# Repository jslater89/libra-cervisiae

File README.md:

# Libra Cervisiae

Libra Cervisiae is an ESP8266-powered microcontroller for reading output from a high-precision scale, used to weigh beer to measure the progress of its fermentation.

Development updates can be found at the project's [github pages site](https://jslater89.github.io/libra-cervisiae).

## History
Libra Cervisiae used to be Pendulum, which was itself once a tilting hydrometer (abandoned for patent reasons) and once a weigh-a-sinker hydrometer (abandoned for DIY difficulty reasons).

Libra Cervisiae has its root in experiments done in the 1990s on measuring fermentation progress by CO2 production, and more recent experiments done by forumgoers at [Homebrewtalk](https://www.homebrewtalk.com/forum/threads/estimating-alcohol-by-total-weight-during-fermentation.265716/#post-6913352) and [Hobbybrouwen.nl](https://www.hobbybrouwen.nl/forum/index.php/topic,35958.0.html).

## Design
Libra Cervisiae is a microcontroller and PCB project. The project is designed with easy DIY in mind, and as such, the PCB uses large, easy-to-solder surface mount components, as well as breakout boards for the major, non-ESP8266 integrated circuits.

The project as specified here includes building a scale of your own, but the microcontroller's design ought to allow for hacking existing scales of the correct capacity, too.

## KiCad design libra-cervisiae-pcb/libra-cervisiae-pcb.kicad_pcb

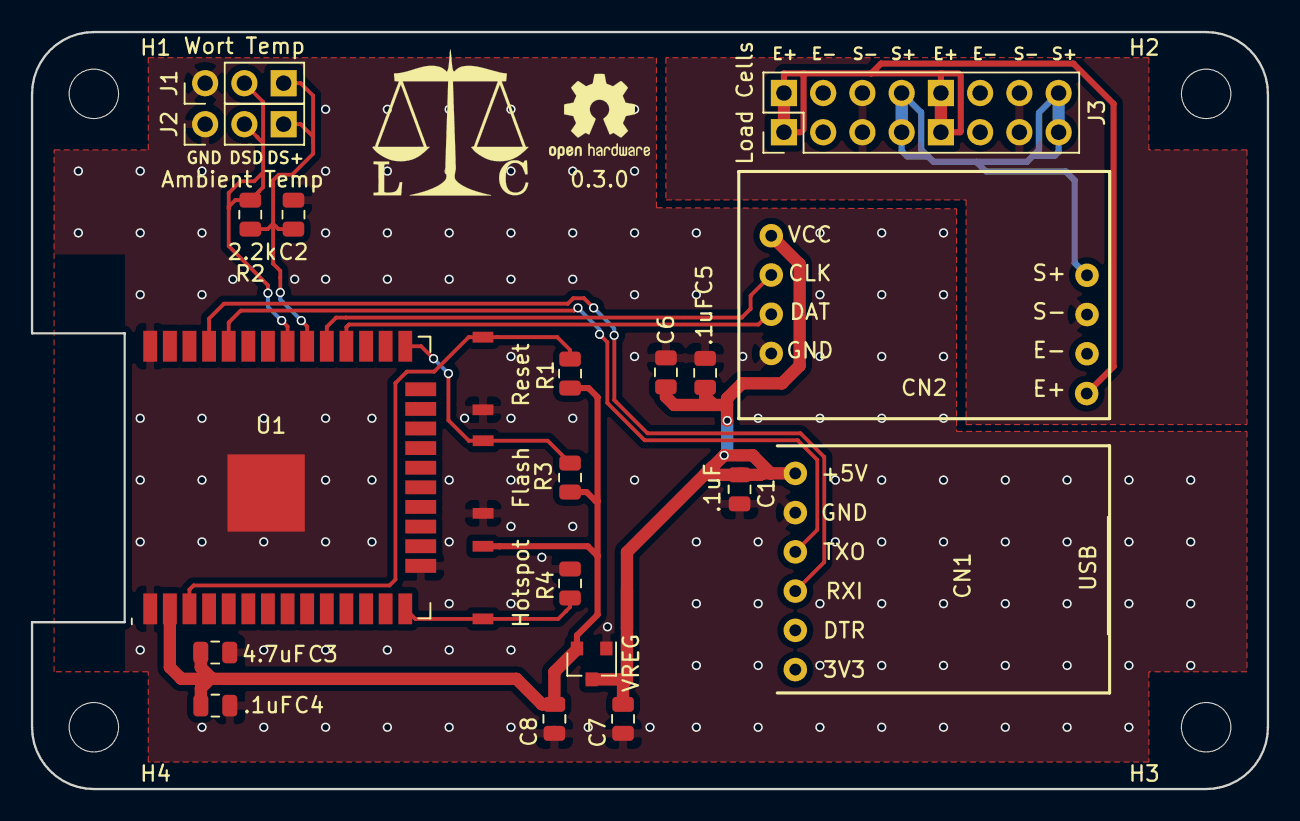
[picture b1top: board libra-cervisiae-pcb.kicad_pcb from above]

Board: 2 copper layers, 80.0 x 49.0 mm, 26 parts (0 on the bottom side), 16 nets.

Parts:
C1, C4, C5: .1uF; C_0805_2012Metric
C2, C6, C7, C8: 1uF; C_0805_2012Metric
C3: 4.7uF; C_0805_2012Metric
CN1: CP2102-BREAKOUT
CN2: HX711_BREAKOUT; HX711-MINI
H1, H2, H3, H4: MountingHole_3.2mm_M3
J1: Wort Temp; PinHeader_1x03_P2.54mm_Vertical
J2: Ambient Temp; PinHeader_1x03_P2.54mm_Vertical
J3: Load Cells; PinHeader_2x08_P2.54mm_Vertical
R1, R3, R4: 10k; R_0805_2012Metric
R2: 2.2k; R_0805_2012Metric
SW1: Reset; 4x3_Switch
SW2: Flash; 4x3_Switch
SW3: Hotspot; 4x3_Switch
U1: ESP32-WROOM-32
U2: VREG; SOT-23

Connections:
/3.3+: C3.2, C4.2, C8.2, R1.2, R3.2, SW3.1, U1.2, U2.2
/CLK: CN2.9, U1.29
/DAT: CN2.8, U1.28
/DS+: C2.2, J1.3, J2.3, R2.2, U1.30
/DSD: J1.2, J2.2, R2.1, U1.31
/E+: CN2.1, J3.1, J3.5, J3.9, J3.13
/E-: CN2.2, J3.2, J3.6, J3.10, J3.14
/GND: C1.1, C2.1, C3.1, C4.1, C5.1, C6.1, C7.1, C8.1, CN1.5, CN2.10, J1.1, J2.1, R4.1, SW1.2, SW2.1, U1.1, U1.15, U1.38, U1.39, U2.1
/HostRX: CN1.3, U1.35
/HostTX: CN1.4, U1.34
/S+: CN2.4, J3.4, J3.8, J3.12, J3.16
/S-: CN2.3, J3.3, J3.7, J3.11, J3.15
/USB+: C1.2, C5.2, C6.2, C7.2, CN1.6, CN2.7, U2.3
unnamed: R1.1, SW1.1, U1.3
unnamed: R3.1, SW2.2, U1.25
unnamed: R4.2, SW3.2, U1.14

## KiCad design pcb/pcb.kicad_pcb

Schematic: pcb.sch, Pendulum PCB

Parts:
C1, C5: 47uF; C_0805_2012Metric
C2, C3, C4, C8: 1uF; C_0805_2012Metric
C6, C7: 100nF; C_0805_2012Metric
CN1: CP2102-BREAKOUT
CN2: TP4056
CN3: HX711_BREAKOUT; HX711-MINI
D1: SS36; D_SMA
J1: BAT+; SolderWirePad_single_SMD_5x3mm
J2: BAT-; SolderWirePad_single_SMD_5x3mm
J3: Battery; Molex_PicoBlade_53048-0410_1x02_P1.25mm_Horizontal
J4: DS18B20; Molex_PicoBlade_53048-0610_1x03_P1.25mm_Horizontal
J5: TMP+; SolderWirePad_single_SMD_5x3mm
J6: TMPO; SolderWirePad_single_SMD_5x3mm
J7: TMP-; SolderWirePad_single_SMD_5x3mm
J8: WHT; SolderWirePad_single_SMD_5x3mm
J9: BLK; SolderWirePad_single_SMD_5x3mm
J10: GRN; SolderWirePad_single_SMD_5x3mm
J11: RED; SolderWirePad_single_SMD_5x3mm
J12: Load Cell; Molex_PicoBlade_53048-0810_1x04_P1.25mm_Horizontal
Q1: AO3401; SOT-23
R1, R4, R5, R6, R7, R8, R9: 10k; R_0805_2012Metric
R2: 120k; R_0805_2012Metric
R3: 390k; R_0805_2012Metric
SW1: Reset; 4x3_Switch
SW2: Flash; 4x3_Switch
U1: VREG; SOT-23
U2: ESP-12F; ESP-12E

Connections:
/3.3+: C1.1, C3.2, R1.1, R4.2, R5.1, R7.1, U1.2 (VO), U2.8 (VCC)
/ADC: C7.1, R2.1, R3.1, U2.2 (ADC)
/BAT+: CN2.4, J1.1, J3.1, R3.2
/BLK: CN3.2, J9.1, J12.3
/CHG+: CN2.3, Q1.3 (D)
/CLK: CN3.9, U2.14 (GPIO5)
/DAT: CN3.8, U2.13 (GPIO4)
/DS+: C4.2, J4.3, J5.1, R9.1, U2.5 (GPIO14)
/DSD: J4.2, J6.1, R9.2, U2.6 (GPIO12)
/GND: C1.2, C2.1, C3.1, C4.1, C5.2, C6.1, C7.2, C8.1, CN1.5, CN2.2, CN2.6, CN3.10, J4.1, J7.1, R2.2, R6.1, R8.2, SW1.2, SW2.2, U1.1 (GND), U2.9 (GND)
/GRN: CN3.4, J10.1, J12.1
/HX+: C8.2, CN3.7, U2.7 (GPIO13)
/HostRX: CN1.3, U2.16 (TXD)
/HostTX: CN1.4, U2.15 (RXD)
/RED: CN3.1, J11.1, J12.4
/USB+: C6.2, CN1.6, CN2.1, D1.2, Q1.1 (G), R8.1
/VREG+: C2.2, C5.1, D1.1, Q1.2 (S), U1.3 (VI)
/WHT: CN3.3, J8.1, J12.2
unnamed: CN2.5, J2.1, J3.2
unnamed: R1.2, SW1.1, U2.1 (REST), U2.4 (GPIO16)
unnamed: R4.1, U2.3 (CH_PD)
unnamed: R5.2, U2.11 (GPIO2)
unnamed: R6.2, U2.10 (GPIO15)
unnamed: R7.2, SW2.1, U2.12 (GPIO0)

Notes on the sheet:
Battery Pads
MCP1700
Load Cell
Battery Monitor
DS18B20 Molex/Pads
Battery Disconnector

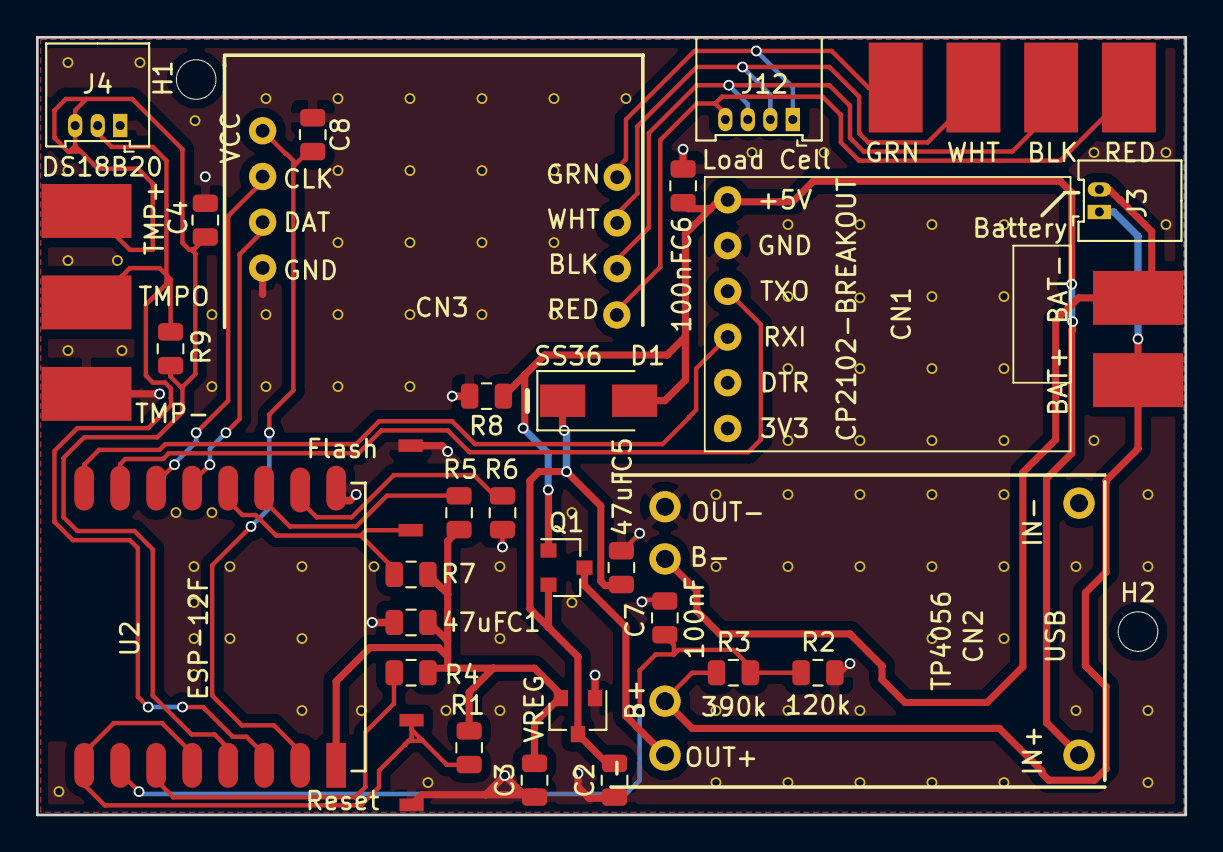
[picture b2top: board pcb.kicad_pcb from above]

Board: 2 copper layers, 63.8 x 43.2 mm, 40 parts (0 on the bottom side), 24 nets.

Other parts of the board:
H1, H2: MountingHole_2.2mm_M2

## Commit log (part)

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2018-05-28 Reorg
2018-05-28 Minor readme update
2018-05-28 README shopping list
2018-05-28 Dummy out some config stuff
2018-05-31 Update config
2018-06-01 Config/hotspot updates, config web page
2018-06-02 README merge
2018-06-03 Add default config file, correct JSONification in main.html
2018-06-03 Add a sensor-handling class for MPU6050 startup/shutdown
    Expects to find the MPU6050 on D5/GPIO14.
2018-06-04 Add voltage reading from A0
    (Wire with a 100kohm resistor.)
2018-06-06 Add output, API config, fix wifi reconnection
2018-06-11 Further shopping list improvements
2018-06-11 Set theme jekyll-theme-slate
2018-06-11 Docs folder
2018-06-14 A custom PCB is probably the best solution in the long run...
    ... so I went ahead and figured one out. Obviously not worth messing
    around with until I've done the whole thing on a breadboard.
2018-06-14 Move KiCad libraries into project
2018-06-14 Move a resistor to line up with another resistor
2018-06-14 Some ongoing minor PCB edits
2018-06-14 PCB blog post
2018-06-15 Clean up traces/vias
2018-06-15 3D model, hide some switch text
2018-06-15 Tweak switch silkscreen labels, add polarity sign to capacitor
    The MCP1700 says a ceramic capacitor is fine, but in case people use
    polar capacitors, it's nice to have an indicator of which way it goes.
    For the switches, remove the redundant SW1/2 label beneath Flash/Reset,
    and just label inside the switch footprint.
2018-06-15 Route I2C traces on opposite side of PCB from ESP-12
    Hopefully to limit interference.
2018-06-15 Further trace cleanup
2018-06-15 Fix problems from Capacitors 101
2018-06-16 Battery etc. blog post
2018-06-16 PCB: use a smaller FTDI breakout board
    The CP2102 USB Micro breakout boards look like they fit between the
    pins of the TP4056 breakout board, which simplifies installation.
2018-06-17 More trace cleanup:
    1. Remove right angles
    2. Thicker USB+/-, charger +/-, 3.3, GND traces
    3. Improve 3.3 and GND routing: more like rails and traces to
    components, less daisy-chaining
2018-06-17 GY521 dimensions update (to match measured size on my workbench)
2018-06-18 Move board in page (ugh)
2018-06-18 Backup file
2018-06-18 Some significant design changes
    Thanks to u/Triabolical_ and u/alez from r/PrintedCircuitBoards for their
    feedback and advice.
    1. Switch to 805 resistors and the non-hand-soldered PCB pad footprints
    They're not appreciably harder to solder, given that they're only 0.01"
    smaller than the 1206 size, and they make routing considerably easier.
    The non-hand-soldered size will be a bit trickier, but not all that
2018-06-18 Add board name, version number, and OSHW logo
2018-06-18 Flip USB-to-serial board so that USB port points outward
2018-06-18 rev 1.0.0-rc.1
2018-06-19 Notes on Tilt patents etc.
2018-06-20 Patent-unencumbered PCB concept
    Tilting is off the table, so let's explore a different idea: weighing
    a sinker immersed in the wort. See the github pages plog for more.
2018-06-20 PCB 1.0.0-rc.2
2018-06-20 README update
2018-06-20 Add a pad for a decoupling capacitor for temperature sensor, just in case
2018-06-20 Measure some pictures of chips to update local parts libraries
    Hopefully it's good enough. Otherwise we'll fix it in rev2.
2018-06-21 Fix some design errors, including a missing connection from 16->RST
2018-06-21 Pendulum Reborn blog post
2018-06-21 Switch to p-channel MOSFET for battery monitor switch
    Because we want as close to zero voltage through the circuit to the
    ADC as possible when the battery monitor is off and the temperature
    sensor is on, we need to switch on the high side, between BAT+ and
    ADC.
    The BSS84 seems like a reasonable choice; its maximum gate threshold
    voltage is well below the difference between ground and a discharged
2018-06-22 DS18B20, 4x3 switch footprint, routing tweaks
    Use a DS18B20 temperature sensor instead of a TMP36. We have enough
    GPIOs—we can drive it from the former SENS2 net (power for the prior
    sensor) and use the former SENS1 net (battery monitor transistor) for
    the data line. This simplifies the ADC circuitry significantly, and
    lets us ditch a bunch of parts.
    Add 4mmx3mm switch footprint, adjust routing as needed.
2018-06-22 PCB.bak
2018-06-24 Another crack at a battery disconnector circuit
    I found an example on the Arduino forums (link at end). It uses a
    p-channel MOSFET 'backwards', with source connected to the load
    and drain to the battery. The parasitic diode therefore blocks
    leakage back into the battery. USB is connected to the gate and also
    to the load, the latter via Schottky diode, to prevent battery
    voltage from sneaking back through the circuit to flip the MOSFET.
2018-06-24 pcb-1.0.0-rc.3
2018-06-25 Switch to 1206 footprint for Schottky diode; 0805 seems hard to find
    At least at the rated power we need (up to about 500ma).
2018-06-25 Fix unconnected pad
2018-06-26 pcb-1.0.0-rc.4
    Just a few final tweaks—labeling, adding a capacitor across USB
    in for filtering.
2018-06-26 pcb-1.0.0-rc.5, blog post
2018-06-28 Bite the bullet and go to a full-backside ground pour
    This also involves removing some unnecessary vias and traces
    routed on the back of the board. Where possible, power and signal
    lines run over ground pour.
2018-06-28 Some further bottom trace reductions
    Break up some islands in the pour so that the return paths are
    closer to the traces.
2018-06-28 pcb-1.0.0-rc.6
2018-06-28 Logos!
2018-06-29 Move PCB text
2018-06-29 Wee tiny tweaks
2018-07-02 pcb-1.0.0-rc.7
2018-07-03 Move to KiCad 5
2018-07-04 Add 3D models for headers, connectors, and buttons
    Not for the boards, but those aren't as trivial as just picking
    3D models for the various footprints here.
2018-07-04 PCB pictures for README
2018-07-06 Fix HX711 footprint (part 1)
    I have a few on hand now, so I can also do actual measurements.
    Once I borrow some calipers again, anyway.
2018-07-06 Redo zone fill after changing footprint
2018-07-07 Add a 10k pullup resistor to DSD/DS+
    Testing reveals that such a thing is needed.
2018-07-08 Rewrite software to use HX711 and DS18B20
2018-07-08 Debug timings, hotspot mode live data tweak
    Debug option to print out timings while running in hydrometer
    mode.
    Hotspot mode live data no longer reads sensors on request;
    instead, it reads ~once per read interval, and reports cached
    data. (This saves on processing time. The reads take a long
    time.)
2018-07-08 Hotspot mode behavior changes and wifi refactoring
    Hotspot mode now tries to connect to the configured wifi network.
    It uses the hydrometer name as its mDNS name. If it connects
    to a wifi network, it'll try to send updates to a server
    in addition to playing local web server.
    Moved wifi connection to a separate function for code reuse.
2018-07-09 Switch to DoubleMatrixMath
    DoubleMatrixMath is a copy of the MatrixMath library which replaces
    floats with doubles, for use on platforms where double is higher-
    precision than float. (Such as the ESP8266.) Uploading that to
    Github soon.
2018-07-09 Add a smoothing capacitor across the HX711 VCC/GND
2018-07-10 README for the software side
2018-07-10 README update for patent stuff
2018-07-11 Temperature compensation config, live webpage bugfixes
2018-07-12 Loadcells blog post
2018-07-13 Move the HX711 capacitor for easier soldering
2018-07-13 Add gravity scale factor for tilt compensation
2018-07-13 Test scale factor, add UI for configuring
    Seems to work as expected, pretty much.
2018-07-16 Route some traces for less ground plane breakage
2018-07-20 Libra Cervisiae logo, relayout
2018-07-20 Libra Cervisiae: add a temperature sensor to the board
    Optional, but recommended: can be used to correct load cell
    output for ambient temperature changes.
2018-07-21 Remove battery connector, charging circuit
2018-07-21 Move connectors a little bit
2018-07-21 Move some labels around
2018-07-23 Versioning, silkscreen changes
2018-07-24 Separate board and wort temperature sensors
2018-07-24 Logo, PCB image
2018-07-27 Fix tare, very rough crack at actual scale output
2018-07-27 Calibration first pass
2018-07-28 app.js and style.css for the web app
2018-07-28 Embed old version of ArduinoJson for ease of building
    The required version is 5.13.2.
2018-07-28 Web app work
2018-07-28 Config entries for scale stuff
2018-07-28 Save more config, search for temp sensors
2018-07-28 Output changes
    1. Include weight in Graviton output
    2. Include raw and calibrated weight in live data output
2018-07-29 Web app scale management
2018-07-29 Interactive bill of materials
2018-07-29 Rewrite calibration to be a long-running process
    In the same manner as tare, calibration should average over
    a larger amount of time to get a better reading.
2018-07-29 Calibration stuff, temperature sensors part 1
    1. Calibration: fix some bugs
    2. Temperature sensors: handle addresses correctly
    Still to do: saving and restoring addresses correctly
2018-07-29 Store addresses in config as longs
2018-07-30 Temp sensors endpoint which, at least, compiles
    Also, improve sensor startup.
2018-07-30 Fix bug in temperature sensor output
2018-07-30 Broken, but moving toward string IDs for temperatures
2018-07-30 Length argument for convertUint8ToLong/vice versa
2018-07-30 Temp sensor web app page
2018-07-31 Finish sensor selection, add wort/board temp to live update
2018-07-31 Groovy logger, move dev-chrome script out of data
    The data dir goes onto the ESP flash, remember.
2018-07-31 Turn off DS18xxx debugging
2018-08-01 Calculations for ABW->ABV->gravity
    Only ABW is super-trustworthy.
2018-08-01 Some adjustments to PCB-mode defines
2018-08-01 Fix board/wort sensor selection
2018-08-01 Generate some test ABW/ABV/gravity numbers, push to live update
2018-08-02 Temperature compensation, batch-starting
2018-08-02 Final fixes for temperature compensation and batch starting
2018-08-02 Update a comment
2018-08-02 "Pendulum" -> "Libra Cervisiae" in web app
2018-08-03 Testing begins blog post
2018-08-03 Some PCB tweaks based on measuring the breakout boards
2018-08-04 PCB cleanup (tracks, lines)
2018-08-04 Fix compile error
2018-08-05 PCB stitching via tweaks
2018-08-05 Measure HX711 with calibers, update footprint, PCB 0.1.1
2018-08-08 Make mounting holes and stitching vias virtual footprints
    That way they don't show up in the BOM, which is also updated.
2018-08-09 Renumber parts to hit actual number of parts on board
2018-08-10 Fix repeated tares, calibrations
    Forgot to reset the average-steps variable.
2018-08-15 Untested Google Drive output
2018-08-16 Use flashstrings for most constant text
    Claw back some heap space; hopefully with enough of this, we can
    do HTTPS
2018-08-16 Remove extra ArduinoJson files, more string memory saving
2018-08-16 Dynamically allocate webserver, free it when doing HTTPS
    Hopefully that'll get us enough memory to do HTTPS output.
2018-08-16 Fix some perilously dumb pointer use
2018-08-16 Yank HTTPSRedirect
2018-08-16 Remove old pcb backup
2018-08-30 Some fixes to the on-device web stuff, based on testing
2018-08-30 Some minor changes to libra-cervisiae.h
2018-08-30 Re-enable scale after discovering pins defs were backward
    Oops
2018-08-30 Ignore exceptions in groovyLogger
2018-08-31 Switch to pin headers/dupont connectors
    The wee JST things I bought are next to impossible to do without
    specialized tools.
2018-09-01 PCB 0.2.0 release
2018-09-05 Turn off debug options
2018-09-05 Minor groovyLogger changes
2018-09-13 Fix some labeling alignment
2019-04-05 Rejigger the load cell e+/s+ traces for approximately equal length
    Is that important? Beats me, but it's worth a shot.
2019-07-26 Fix a blog post which has been broken for a year
2019-08-08 Draft post for PCB test successes
2019-08-09 Use thicker traces to the load cell connectors
2019-08-09 Fatten load cell traces
2019-08-16 0.3.0 schematic/layout
    1. Bump board capacitance down for USB inrush current reasons
    The previous 47uF capacitor on the board worked on one of my PCs
    but not the other. Swap it for a 4.7uF cap, which sneaks us in
    just under the 10uF limit the USB spec requires.
    2. Version numbers up
    The ESP32 change is significant enough to warrant it.
2019-09-11 Add a Hotspot button to restart into hotspot mode
2019-09-12 Add title to blog post file
2019-09-12 Ensure a via-free path from CP2012 to MCP1700
    That seems like a recipe for making a super-hot via.
2019-09-12 Update README.md
    PCB 0.3.0 picture instead.
